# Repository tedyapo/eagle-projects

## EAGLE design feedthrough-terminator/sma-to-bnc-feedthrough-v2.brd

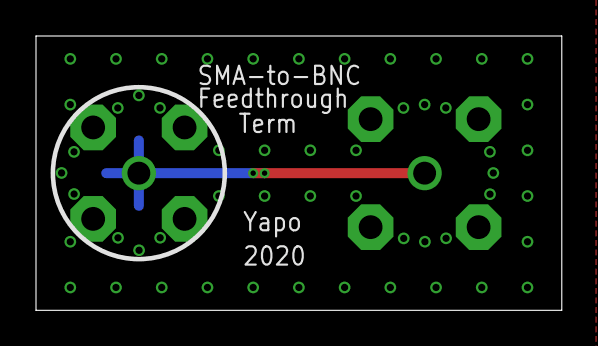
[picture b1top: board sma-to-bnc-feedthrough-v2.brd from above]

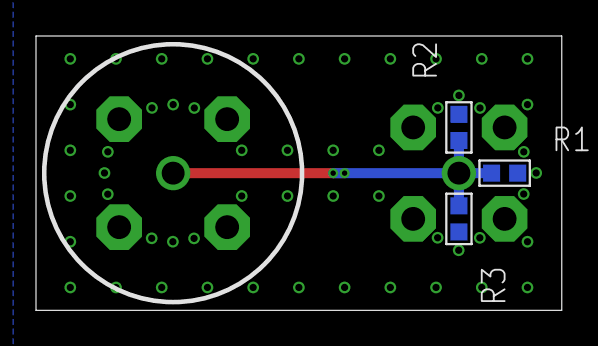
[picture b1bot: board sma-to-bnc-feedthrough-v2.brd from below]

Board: 2 copper layers, 29.2 x 15.2 mm, 5 parts (4 on the bottom side), 2 nets.

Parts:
J1: SMA_FEMALE_RA; SMA_RA_PCB
J2: BNC-M; BNC_MALE_PCB
R1, R2, R3: 150; R0603

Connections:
GND: J1.SHIELD@1, J1.SHIELD@2, J1.SHIELD@3, J1.SHIELD@4, J2.SHIELD@1, J2.SHIELD@2, J2.SHIELD@3, J2.SHIELD@4, R1.P$2, R2.P$2, R3.P$2
unnamed: J1.CENTER, J2.CENTER, R1.P$1, R2.P$1, R3.P$1

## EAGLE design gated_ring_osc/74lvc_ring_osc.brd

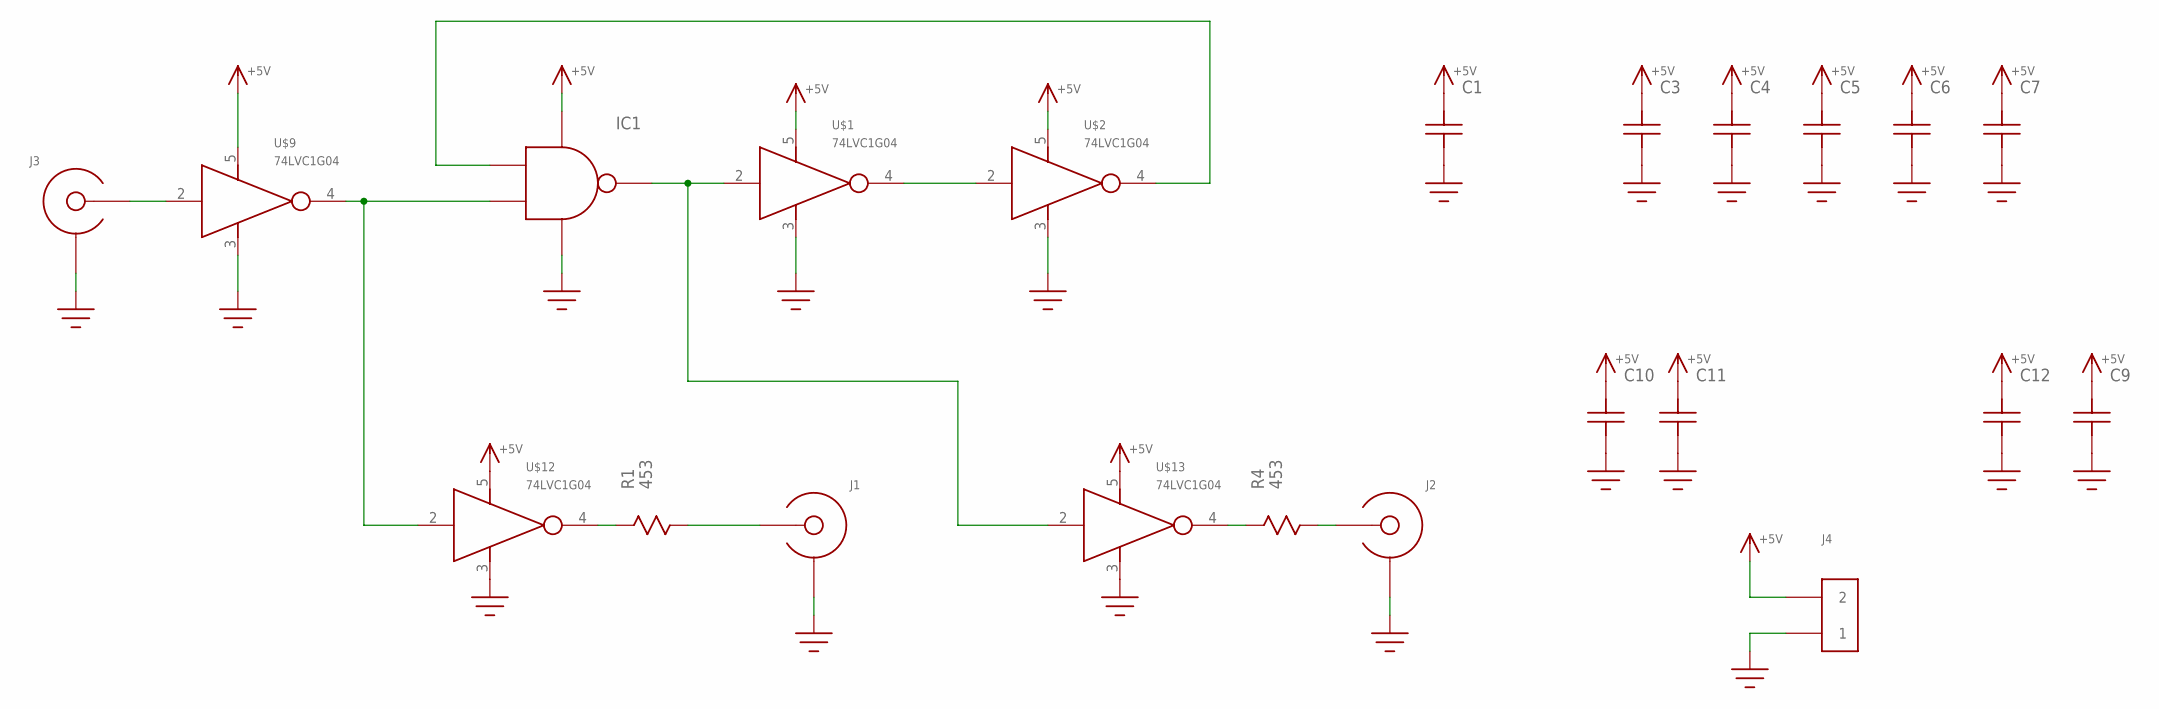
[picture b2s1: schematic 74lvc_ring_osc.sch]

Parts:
C1, C3, C4, C5, C6, C7: C0603
C9, C12: C1206; 1206
C10, C11: C0805; 0805
IC1: 74LVC1G00; SOT23-5
J1, J2, J3: EDGE_LAUNCH_JACK; EDGE_LAUNCH_RF_CON
J4: HEADER_2PIN
R1, R4: 453; R0805
U$1, U$2, U$9, U$12, U$13: 74LVC1G04; SOT23-5

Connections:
+5V: C1.P$2, C3.P$2, C4.P$2, C5.P$2, C6.P$2, C7.P$2, C9.P$2, C10.P$2, C11.P$2, C12.P$2, IC1.5 (VCC), J4.2, U$1.5 (VCC), U$2.5 (VCC), U$9.5 (VCC), U$12.5 (VCC), U$13.5 (VCC)
GND: C1.P$1, C3.P$1, C4.P$1, C5.P$1, C6.P$1, C7.P$1, C9.P$1, C10.P$1, C11.P$1, C12.P$1, IC1.3 (GND), J1.GND@1 (SHIELD), J1.GND@2 (SHIELD), J1.GND@3 (SHIELD), J1.GND@4 (SHIELD), J1.GND@5 (SHIELD), J1.GND@6 (SHIELD), J1.GND@7 (SHIELD), J1.GND@8 (SHIELD), J1.GND@9 (SHIELD), J1.GND@10 (SHIELD), J1.GND@11 (SHIELD), J1.GND@12 (SHIELD), J1.SHIELD@1 (SHIELD), J1.SHIELD@2 (SHIELD), J2.GND@1 (SHIELD), J2.GND@2 (SHIELD), J2.GND@3 (SHIELD), J2.GND@4 (SHIELD), J2.GND@5 (SHIELD), J2.GND@6 (SHIELD), J2.GND@7 (SHIELD), J2.GND@8 (SHIELD), J2.GND@9 (SHIELD), J2.GND@10 (SHIELD), J2.GND@11 (SHIELD), J2.GND@12 (SHIELD), J2.SHIELD@1 (SHIELD), J2.SHIELD@2 (SHIELD), J3.GND@1 (SHIELD), J3.GND@2 (SHIELD), J3.GND@3 (SHIELD), J3.GND@4 (SHIELD), J3.GND@5 (SHIELD), J3.GND@6 (SHIELD), J3.GND@7 (SHIELD), J3.GND@8 (SHIELD), J3.GND@9 (SHIELD), J3.GND@10 (SHIELD), J3.GND@11 (SHIELD), J3.GND@12 (SHIELD), J3.SHIELD@1 (SHIELD), J3.SHIELD@2 (SHIELD), J4.1, U$1.3 (GND), U$2.3 (GND), U$9.3 (GND), U$12.3 (GND), U$13.3 (GND)
unnamed: IC1.4 (Y), U$1.2 (IN), U$13.2 (IN)
unnamed: U$1.4 (OUT), U$2.2 (IN)
unnamed: IC1.2 (A), U$2.4 (OUT)
unnamed: IC1.1 (B), U$9.4 (OUT), U$12.2 (IN)
unnamed: R1.P$1, U$12.4 (OUT)
unnamed: R4.P$1, U$13.4 (OUT)
unnamed: J3.CENTER, U$9.2 (IN)
unnamed: J2.CENTER, R4.P$2
unnamed: J1.CENTER, R1.P$2

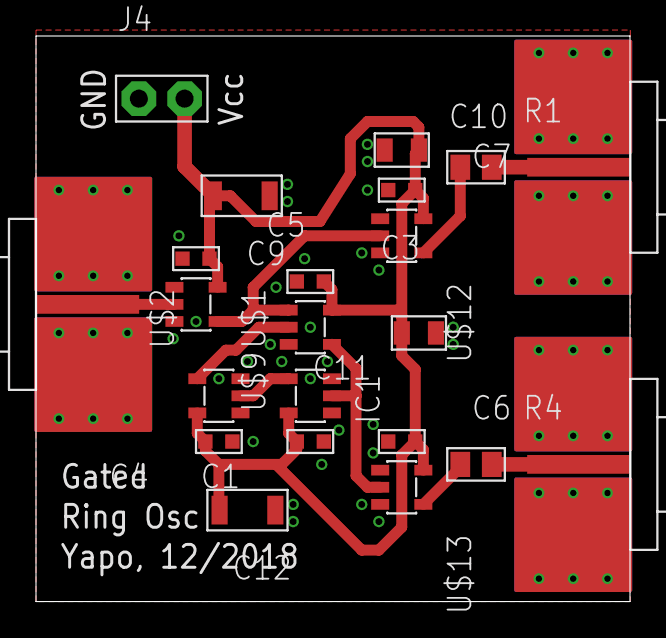
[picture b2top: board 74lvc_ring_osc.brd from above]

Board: 2 copper layers, 33.0 x 31.4 mm, 22 parts (0 on the bottom side), 11 nets.

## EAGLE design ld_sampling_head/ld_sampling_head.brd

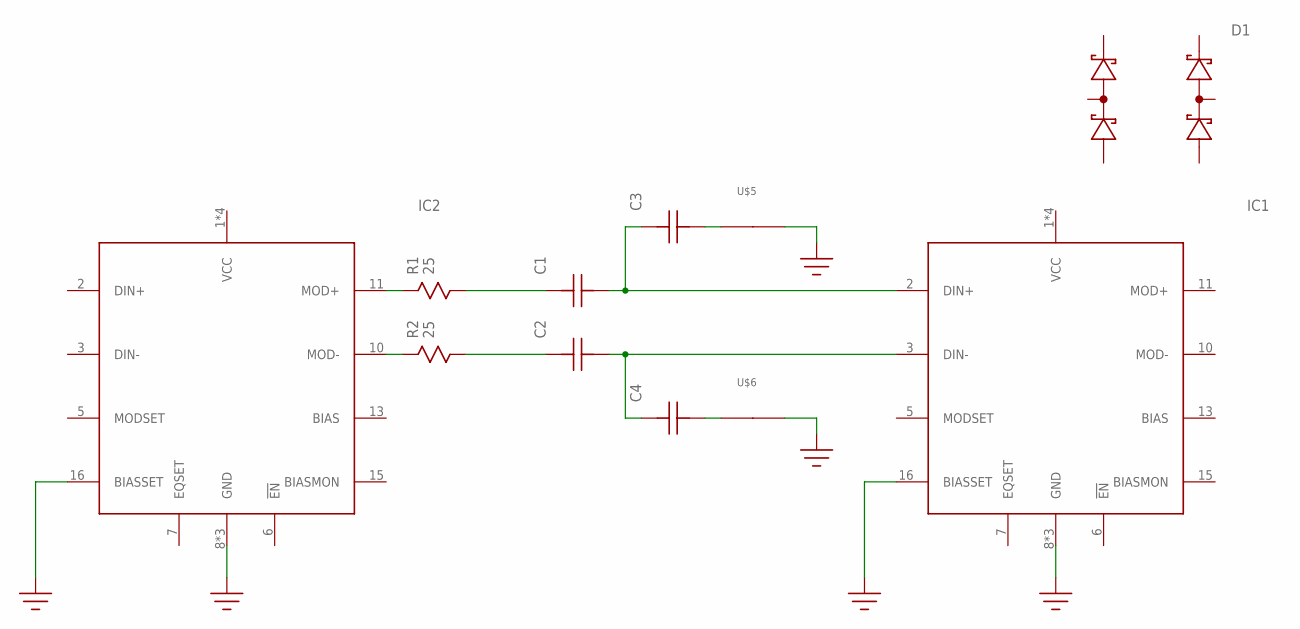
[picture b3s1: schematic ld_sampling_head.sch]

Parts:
C1, C2, C3, C4: C; C0402
D1: SMS3923-081; SC-88
IC1, IC2: SY88022AL; TQFN16-EP
R1, R2: 25; 0402
U$5, U$6: SHORT14MIL; SHORT_14MIL

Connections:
GND: IC1.8 (GND), IC1.14 (GND), IC1.16 (BIASSET), IC1.EP (GND), IC2.8 (GND), IC2.14 (GND), IC2.16 (BIASSET), IC2.EP (GND), U$5.P$2, U$6.P$2
unnamed: IC2.11 (MOD+), R1.1
unnamed: IC2.10 (MOD-), R2.1
unnamed: C1.1, C3.2, IC1.2 (DIN+)
unnamed: C2.1, C4.2, IC1.3 (DIN-)
unnamed: C1.2, R1.2
unnamed: C2.2, R2.2
unnamed: C3.1, U$5.P$1
unnamed: C4.1, U$6.P$1

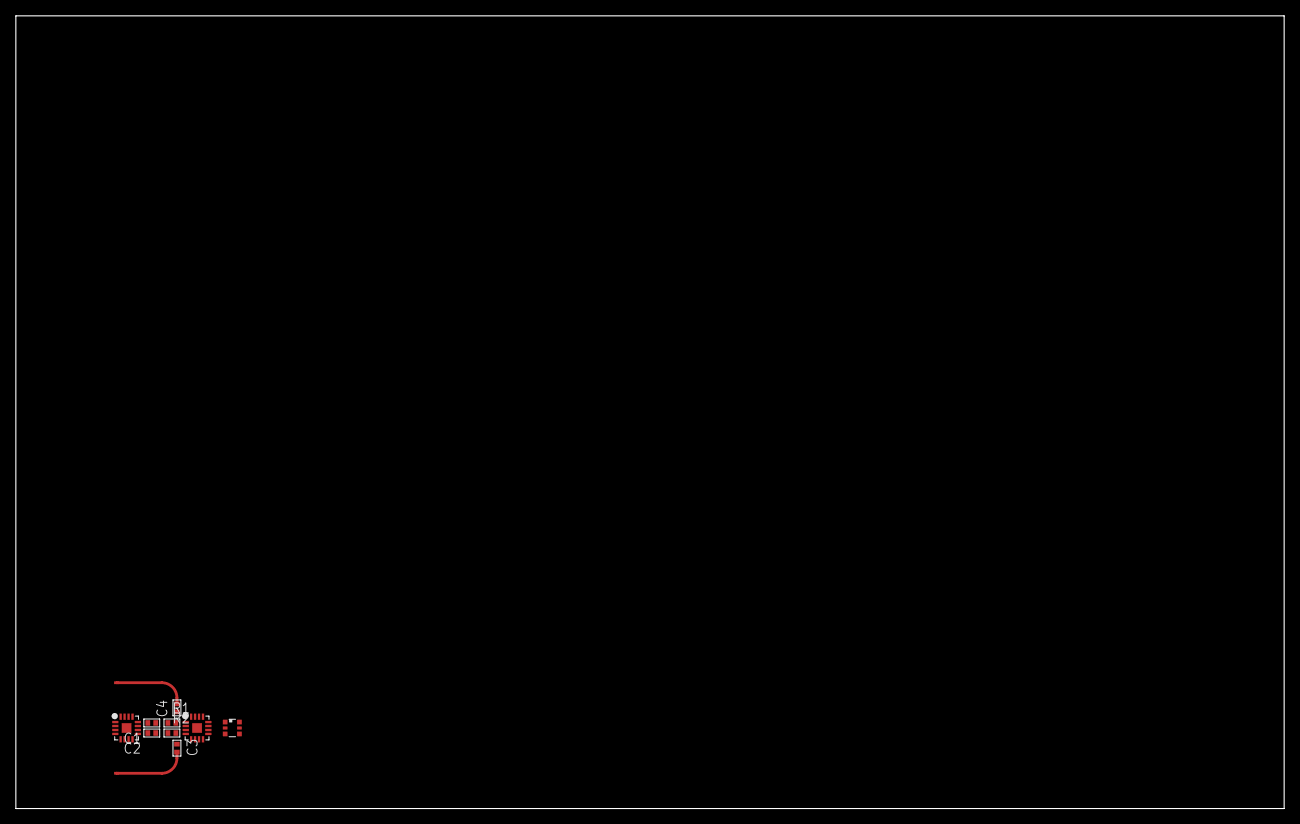
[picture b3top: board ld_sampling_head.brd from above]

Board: 2 copper layers, 160.0 x 100.0 mm, 11 parts (0 on the bottom side), 9 nets.

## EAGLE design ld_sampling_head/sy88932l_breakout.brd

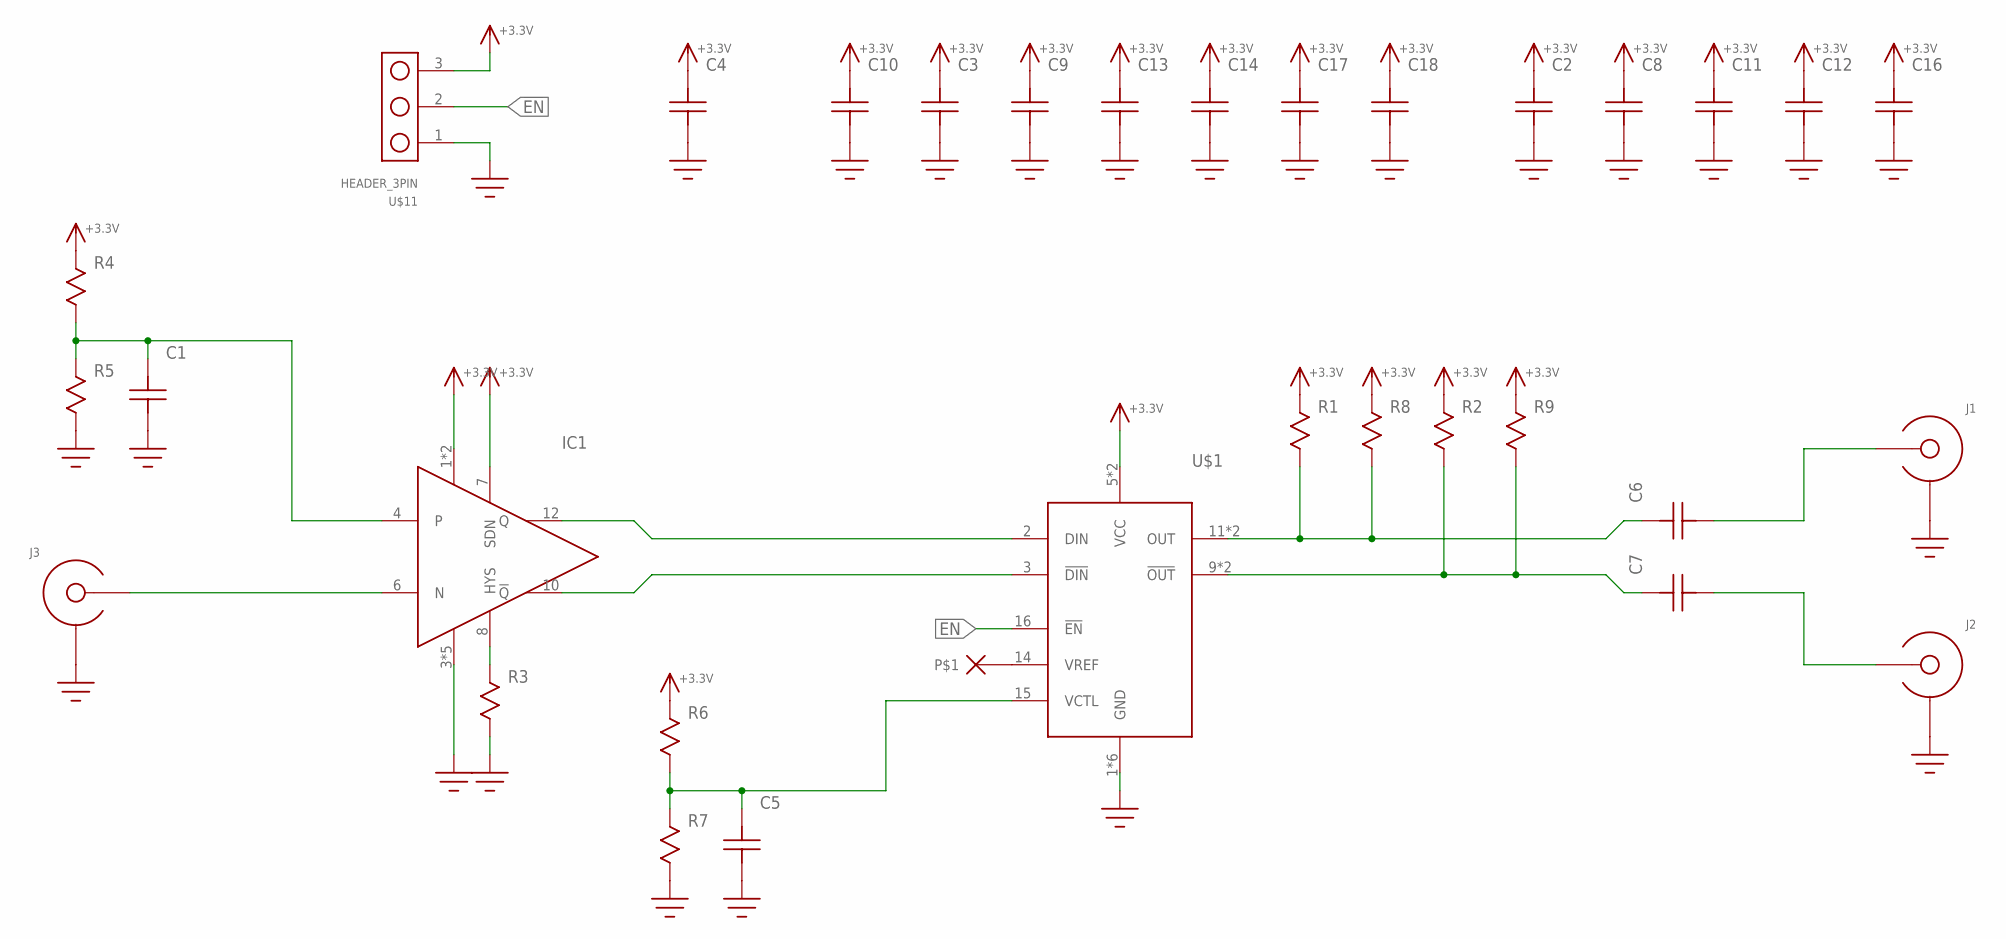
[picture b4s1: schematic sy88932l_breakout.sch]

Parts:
C1, C3, C5, C9, C10, C13, C14, C17, C18: C0603
C2, C6, C7, C8, C11, C12, C16: C; C0402
C4: C1206; 1206
IC1: ADCMP607; QFN12-3X3
J1, J2, J3: SMA_END_LAUNCH4L; SMA_EDGE_LAUNCH
R1, R2, R8, R9: R0402; 0402
R3, R4, R5, R6, R7: R0603
U$1: SY88932L; TQFN16
U$11: HEADER_3PIN

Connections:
!EN!: U$1.16 (!EN!), U$11.2
+3.3V: C2.2, C3.P$2, C4.P$2, C8.2, C9.P$2, C10.P$2, C11.2, C12.2, C13.P$2, C14.P$2, C16.2, C17.P$2, C18.P$2, IC1.1 (VCC), IC1.2 (VCC), IC1.7 (SDN), R1.1, R2.1, R4.P$1, R6.P$1, R8.1, R9.1, U$1.5 (VCC), U$1.6 (VCC), U$11.3
D_N: IC1.10 (!Q!), U$1.3 (!DIN!)
D_P: IC1.12 (Q), U$1.2 (DIN)
GND: C1.P$1, C2.1, C3.P$1, C4.P$1, C5.P$1, C8.1, C9.P$1, C10.P$1, C11.1, C12.1, C13.P$1, C14.P$1, C16.1, C17.P$1, C18.P$1, IC1.3 (VEE), IC1.5 (VEE), IC1.9 (VEE), IC1.11 (VEE), IC1.EP (VEE), J1.BOTTOM_PAD (SHIELD), J1.GND@1 (SHIELD), J1.GND@2 (SHIELD), J1.GND@3 (SHIELD), J1.GND@4 (SHIELD), J1.GND@5 (SHIELD), J1.GND@6 (SHIELD), J1.GND@7 (SHIELD), J1.GND@8 (SHIELD), J1.GND@14 (SHIELD), J1.GND@15 (SHIELD), J1.GND@16 (SHIELD), J1.GND@17 (SHIELD), J1.GND_PAD1 (SHIELD), J1.GND_PAD2 (SHIELD), J2.BOTTOM_PAD (SHIELD), J2.GND@1 (SHIELD), J2.GND@2 (SHIELD), J2.GND@3 (SHIELD), J2.GND@4 (SHIELD), J2.GND@5 (SHIELD), J2.GND@6 (SHIELD), J2.GND@7 (SHIELD), J2.GND@8 (SHIELD), J2.GND@14 (SHIELD), J2.GND@15 (SHIELD), J2.GND@16 (SHIELD), J2.GND@17 (SHIELD), J2.GND_PAD1 (SHIELD), J2.GND_PAD2 (SHIELD), J3.BOTTOM_PAD (SHIELD), J3.GND@1 (SHIELD), J3.GND@2 (SHIELD), J3.GND@3 (SHIELD), J3.GND@4 (SHIELD), J3.GND@5 (SHIELD), J3.GND@6 (SHIELD), J3.GND@7 (SHIELD), J3.GND@8 (SHIELD), J3.GND@14 (SHIELD), J3.GND@15 (SHIELD), J3.GND@16 (SHIELD), J3.GND@17 (SHIELD), J3.GND_PAD1 (SHIELD), J3.GND_PAD2 (SHIELD), R3.P$2, R5.P$2, R7.P$2, U$1.1 (GND), U$1.4 (GND), U$1.7 (GND), U$1.8 (GND), U$1.13 (GND), U$1.EP (GND), U$11.1
unnamed: IC1.8 (HYS), R3.P$1
unnamed: C1.P$2, IC1.4, R4.P$2, R5.P$1
unnamed: IC1.6 (N), J3.CENTER@1 (CENTER), J3.CENTER@2 (CENTER)
unnamed: C5.P$2, R6.P$2, R7.P$1, U$1.15 (VCTL)
unnamed: C6.2, R1.2, R8.2, U$1.11 (OUT), U$1.12 (OUT)
unnamed: C7.2, R2.2, R9.2, U$1.9 (!OUT!), U$1.10 (!OUT!)
unnamed: C6.1, J1.CENTER@1 (CENTER), J1.CENTER@2 (CENTER)
unnamed: C7.1, J2.CENTER@1 (CENTER), J2.CENTER@2 (CENTER)

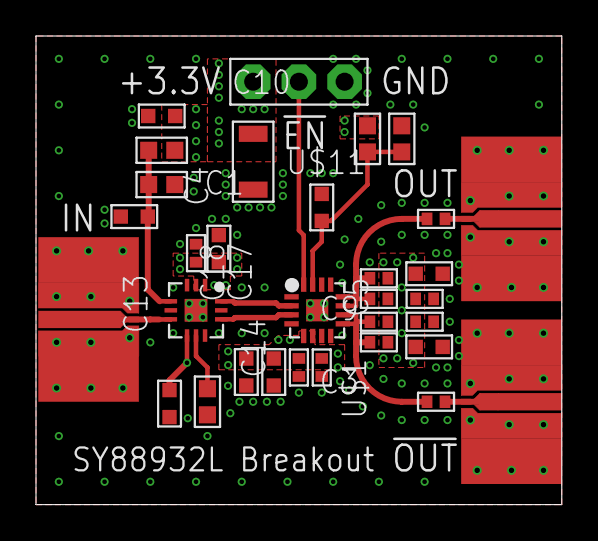
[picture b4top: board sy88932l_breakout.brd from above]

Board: 4 copper layers, 29.2 x 26.0 mm, 32 parts (0 on the bottom side), 13 nets.

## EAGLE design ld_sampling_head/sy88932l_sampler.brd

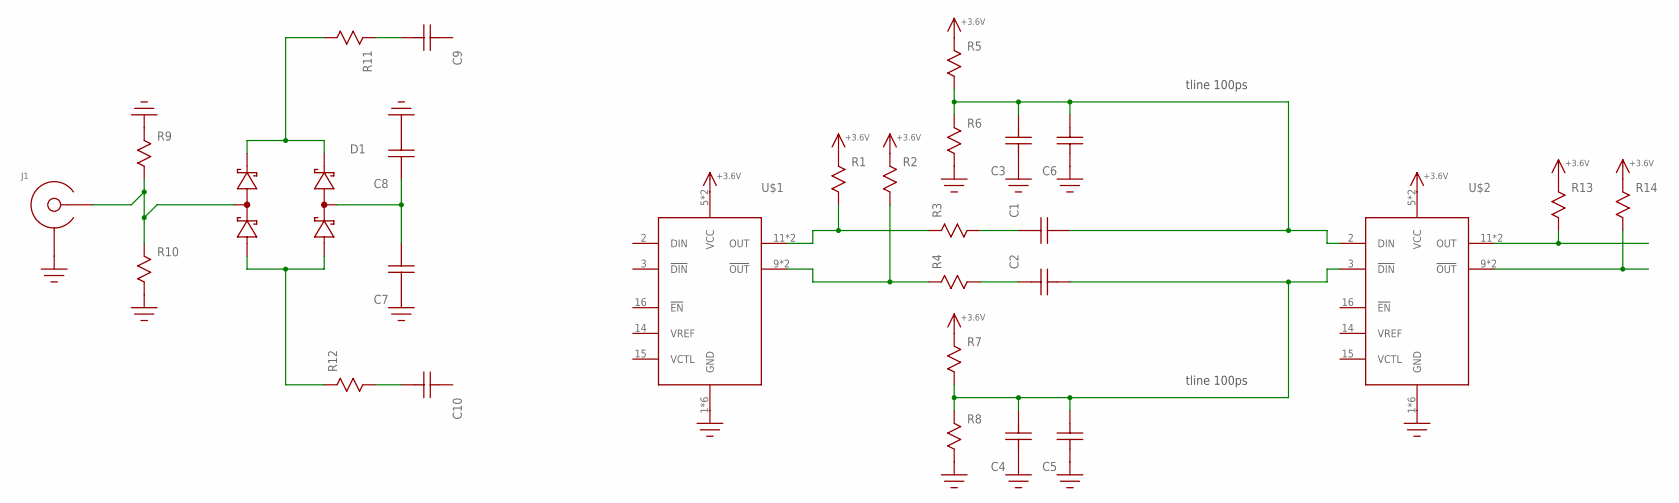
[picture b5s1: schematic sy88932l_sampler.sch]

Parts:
C1, C2, C3, C4: C0603
C5, C6, C7, C8, C9, C10: C; C0402
D1: SMS3923-081; SC-88
J1: SMA_END_LAUNCH4L; SMA_EDGE_LAUNCH
R1, R2, R3, R4, R5, R6, R7, R8, R9, R10, R11, R12, R13, R14: R0603
U$1, U$2: SY88932L; TQFN16

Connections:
+3.6V: R1.P$1, R2.P$1, R5.P$1, R7.P$1, R13.P$1, R14.P$1, U$1.5 (VCC), U$1.6 (VCC), U$2.5 (VCC), U$2.6 (VCC)
GND: C3.P$2, C4.P$2, C5.2, C6.2, C7.2, C8.1, J1.BOTTOM_PAD (SHIELD), J1.GND@1 (SHIELD), J1.GND@2 (SHIELD), J1.GND@3 (SHIELD), J1.GND@4 (SHIELD), J1.GND@5 (SHIELD), J1.GND@6 (SHIELD), J1.GND@7 (SHIELD), J1.GND@8 (SHIELD), J1.GND@14 (SHIELD), J1.GND@15 (SHIELD), J1.GND@16 (SHIELD), J1.GND@17 (SHIELD), J1.GND_PAD1 (SHIELD), J1.GND_PAD2 (SHIELD), R6.P$2, R8.P$2, R9.P$1, R10.P$2, U$1.1 (GND), U$1.4 (GND), U$1.7 (GND), U$1.8 (GND), U$1.13 (GND), U$1.EP (GND), U$2.1 (GND), U$2.4 (GND), U$2.7 (GND), U$2.8 (GND), U$2.13 (GND), U$2.EP (GND)
unnamed: R1.P$2, R3.P$1, U$1.11 (OUT), U$1.12 (OUT)
unnamed: R2.P$2, R4.P$1, U$1.9 (!OUT!), U$1.10 (!OUT!)
unnamed: C1.P$2, R3.P$2
unnamed: C2.P$2, R4.P$2
unnamed: C1.P$1, C3.P$1, C6.1, R5.P$2, R6.P$1, U$2.2 (DIN)
unnamed: D1.5 (COMMON1), J1.CENTER@1 (CENTER), J1.CENTER@2 (CENTER), R9.P$2, R10.P$1
unnamed: C2.P$1, C4.P$1, C5.1, R7.P$2, R8.P$1, U$2.3 (!DIN!)
unnamed: C7.1, C8.2, D1.2 (COMMON0)
unnamed: D1.1 (ANODE0), D1.6 (ANODE1), R12.P$1
unnamed: D1.3 (CATHODE0), D1.4 (CATHODE1), R11.P$2
unnamed: C9.1, R11.P$1
unnamed: C10.1, R12.P$2
unnamed: R13.P$2, U$2.11 (OUT), U$2.12 (OUT)
unnamed: R14.P$2, U$2.9 (!OUT!), U$2.10 (!OUT!)

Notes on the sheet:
tline 100ps

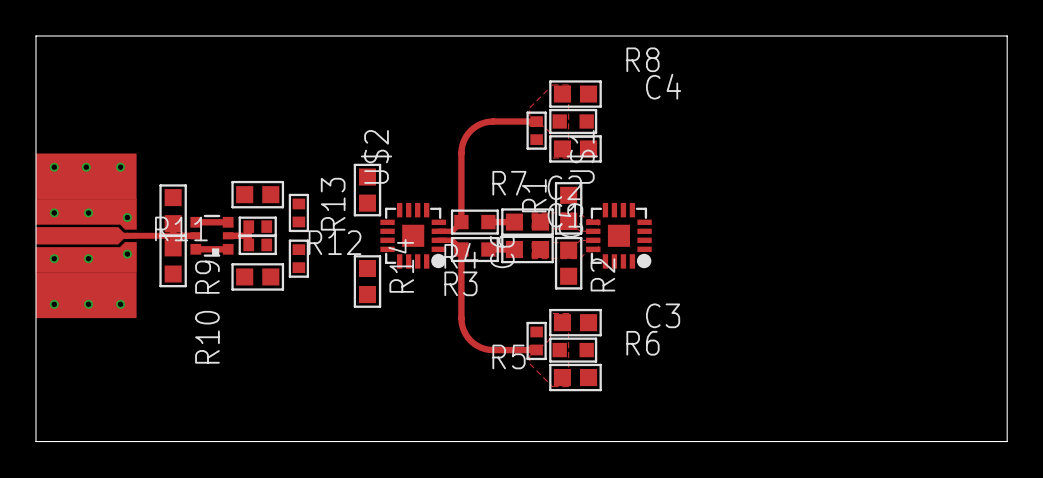
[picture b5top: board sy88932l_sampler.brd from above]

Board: 4 copper layers, 54.0 x 22.5 mm, 28 parts (0 on the bottom side), 16 nets.

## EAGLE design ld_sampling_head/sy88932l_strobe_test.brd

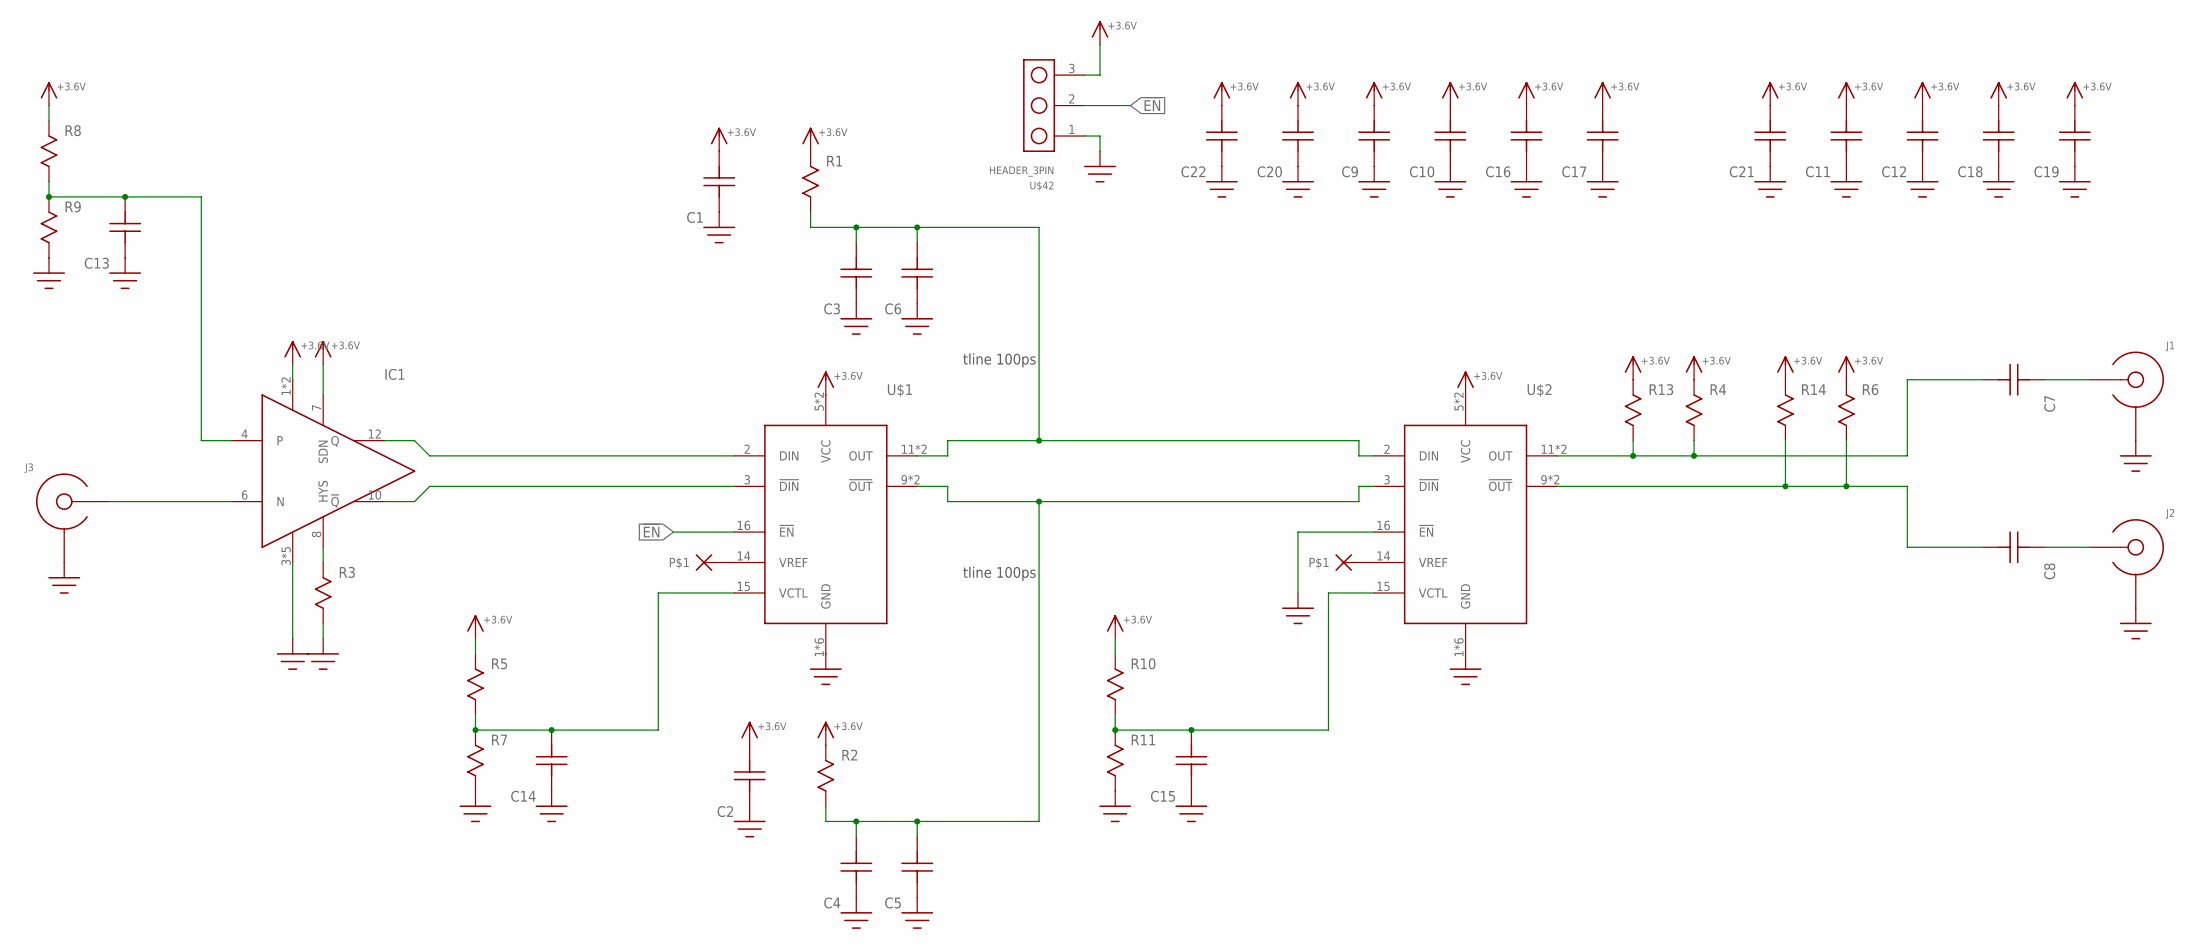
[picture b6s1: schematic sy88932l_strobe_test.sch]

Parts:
C1, C2, C11, C12, C13, C14, C15, C18, C19, C21: C0603
C3, C4, C5, C6, C7, C8, C9, C10, C16, C17, C20: C; C0402
C22: C1206; 1206
IC1: ADCMP607; QFN12-3X3
J1, J2, J3: SMA_END_LAUNCH4L; SMA_EDGE_LAUNCH
R1, R2, R5, R7, R8, R9, R10, R11: R0603
R3, R4, R6, R13, R14: R0402; 0402
U$1, U$2: SY88932L; TQFN16
U$42: HEADER_3PIN

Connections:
!EN!: U$1.16 (!EN!), U$42.2
+3.6V: C1.P$1, C2.P$1, C9.1, C10.1, C11.P$1, C12.P$1, C16.1, C17.1, C18.P$1, C19.P$1, C20.1, C21.P$1, C22.P$1, IC1.1 (VCC), IC1.2 (VCC), IC1.7 (SDN), R1.P$1, R2.P$1, R4.1, R5.P$1, R6.1, R8.P$1, R10.P$1, R13.1, R14.1, U$1.5 (VCC), U$1.6 (VCC), U$2.5 (VCC), U$2.6 (VCC), U$42.3
GND: C1.P$2, C2.P$2, C3.2, C4.2, C5.2, C6.2, C9.2, C10.2, C11.P$2, C12.P$2, C13.P$2, C14.P$2, C15.P$2, C16.2, C17.2, C18.P$2, C19.P$2, C20.2, C21.P$2, C22.P$2, IC1.3 (VEE), IC1.5 (VEE), IC1.9 (VEE), IC1.11 (VEE), IC1.EP (VEE), J1.BOTTOM_PAD (SHIELD), J1.GND@1 (SHIELD), J1.GND@2 (SHIELD), J1.GND@3 (SHIELD), J1.GND@4 (SHIELD), J1.GND@5 (SHIELD), J1.GND@6 (SHIELD), J1.GND@7 (SHIELD), J1.GND@8 (SHIELD), J1.GND@14 (SHIELD), J1.GND@15 (SHIELD), J1.GND@16 (SHIELD), J1.GND@17 (SHIELD), J1.GND_PAD1 (SHIELD), J1.GND_PAD2 (SHIELD), J2.BOTTOM_PAD (SHIELD), J2.GND@1 (SHIELD), J2.GND@2 (SHIELD), J2.GND@3 (SHIELD), J2.GND@4 (SHIELD), J2.GND@5 (SHIELD), J2.GND@6 (SHIELD), J2.GND@7 (SHIELD), J2.GND@8 (SHIELD), J2.GND@14 (SHIELD), J2.GND@15 (SHIELD), J2.GND@16 (SHIELD), J2.GND@17 (SHIELD), J2.GND_PAD1 (SHIELD), J2.GND_PAD2 (SHIELD), J3.BOTTOM_PAD (SHIELD), J3.GND@1 (SHIELD), J3.GND@2 (SHIELD), J3.GND@3 (SHIELD), J3.GND@4 (SHIELD), J3.GND@5 (SHIELD), J3.GND@6 (SHIELD), J3.GND@7 (SHIELD), J3.GND@8 (SHIELD), J3.GND@14 (SHIELD), J3.GND@15 (SHIELD), J3.GND@16 (SHIELD), J3.GND@17 (SHIELD), J3.GND_PAD1 (SHIELD), J3.GND_PAD2 (SHIELD), R3.2, R7.P$2, R9.P$2, R11.P$2, U$1.1 (GND), U$1.4 (GND), U$1.7 (GND), U$1.8 (GND), U$1.13 (GND), U$1.EP (GND), U$2.1 (GND), U$2.4 (GND), U$2.7 (GND), U$2.8 (GND), U$2.13 (GND), U$2.16 (!EN!), U$2.EP (GND), U$42.1
unnamed: IC1.12 (Q), U$1.2 (DIN)
unnamed: IC1.10 (!Q!), U$1.3 (!DIN!)
unnamed: IC1.8 (HYS), R3.1
unnamed: C3.1, C6.1, R1.P$2, U$1.11 (OUT), U$1.12 (OUT), U$2.2 (DIN)
unnamed: C7.2, J1.CENTER@1 (CENTER), J1.CENTER@2 (CENTER)
unnamed: C4.1, C5.1, R2.P$2, U$1.9 (!OUT!), U$1.10 (!OUT!), U$2.3 (!DIN!)
unnamed: C8.2, J2.CENTER@1 (CENTER), J2.CENTER@2 (CENTER)
unnamed: C13.P$1, IC1.4, R8.P$2, R9.P$1
unnamed: IC1.6 (N), J3.CENTER@1 (CENTER), J3.CENTER@2 (CENTER)
unnamed: C14.P$1, R5.P$2, R7.P$1, U$1.15 (VCTL)
unnamed: C7.1, R4.2, R13.2, U$2.11 (OUT), U$2.12 (OUT)
unnamed: C8.1, R6.2, R14.2, U$2.9 (!OUT!), U$2.10 (!OUT!)
unnamed: C15.P$1, R10.P$2, R11.P$1, U$2.15 (VCTL)

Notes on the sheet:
tline 100ps

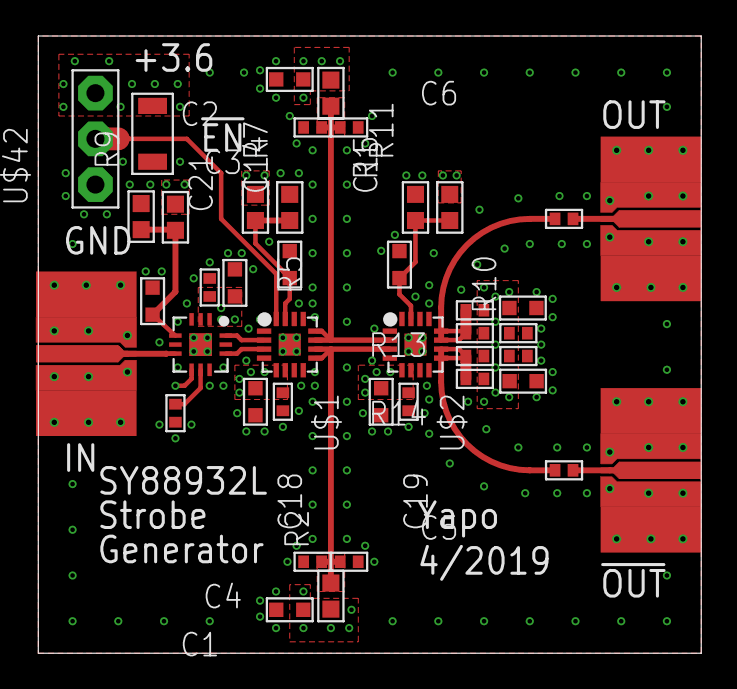
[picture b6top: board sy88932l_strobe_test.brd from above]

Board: 4 copper layers, 36.8 x 34.3 mm, 42 parts (0 on the bottom side), 16 nets.
